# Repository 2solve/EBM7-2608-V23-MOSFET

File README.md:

# IC2S EBM7-2608 V2.3 — variante configurável 0-10 V / 4-20 mA (MOSFET)

Placa de extensão da família IC2S (Extension Board Model 7) com **quatro entradas analógicas configuráveis por software**
(cada uma em 0-10 V **ou** 4-20 mA), **uma entrada de célula de carga** e **um NTC de junta fria**, medidos por um ADC
sigma-delta de 24 bits (**AD7124-8**). Encaixa por baixo na base board: **P1** é o barramento (24 V, 5 V, SPI) e **P2** leva os
sinais de campo.

É a irmã da variante fixa 4-20 mA (repositório `2solve/EBM7-2608-V3`): mesma placa, mesmo layout de base, mais um MOSFET por
canal para escolher o modo e uma protecção completa da alimentação dos sensores.

Projecto KiCad 10 (testado em 10.0.5). Abrir
`Desenvolvimento_IC2S-EBM7-2608-V2.3-MOSFET/Projeto_IC2S-EBM7-2608-V2.3-MOSFET/IC2S-EBM7-2608-V2.3-MOSFET.kicad_pro`.

Identificador desta versão: **`IC2S-EBM7-2608-V2.3-MOSFET`**.

---

## Estado (28-09-2026)

| Verificação | Resultado |
|---|---|
| ERC | 0 erros |
| DRC (`--severity-all --schematic-parity`) | **0 erros**, 67 avisos (serigrafia) |
| Ligações por fazer | **48** |
| Paridade esquemático ↔ PCB | **1** (C35, ver [Pendentes](#pendentes)) |

**O esquemático está fechado; a placa não.** A PCB foi construída sobre a da variante fixa: as 148 peças comuns estão na mesma
posição e com as mesmas pistas; as **20 peças que só existem nesta variante** estão juntas num rectângulo à direita da placa,
à espera de serem colocadas e roteadas. Por isso as pastas de fabricação estão vazias.

---

## Estrutura do repositório

Padrão de pastas dos produtos da 2Solve (o mesmo de `Produtos/Axcel_Sensor`):

```
Desenvolvimento_IC2S-EBM7-2608-V2.3-MOSFET/
├── Projeto_IC2S-EBM7-2608-V2.3-MOSFET/
│   ├── IC2S-EBM7-2608-V2.3-MOSFET.kicad_pro / .kicad_sch / .kicad_pcb / .kicad_dru
│   ├── 01_conectores … 08_ntc.kicad_sch          (as oito folhas)
│   ├── footprints/EBM7_V23.pretty, symbols/       (bibliotecas locais, por ${KIPRJMOD})
│   ├── Documentos_de_Referência-…/                (33 datasheets + catálogo TDK de MLCC)
│   └── Outputs/drc_report.json
├── Documentos_IC2S-EBM7-2608-V2.3-MOSFET/
│   ├── 00-Especificações_Técnicas_…/   registos das alterações (25-09 e 28-09)
│   ├── 01-Esquemáticos_…/              Schematic-….pdf, ….step, …-Top_View.pdf, …-Bottom_View.pdf
│   ├── 02-Pinout_…/                    (vazio)
│   └── 03-Diagrama_Blocos_…/           (vazio)
└── Arquivos_Fabricação_IC2S-EBM7-2608-V2.3-MOSFET/
    ├── 00-Gerbers_…/  01-BOM_List_…/  02-Pick-and-Place_…/  03-Stencil_…/   (vazios até a placa estar roteada)
```

**Onde está cada decisão:** cada folha tem um bloco «DECISOES DESTA FOLHA» com notas numeradas; aqui cita-se *folha N, nota M*.

---

## O que é igual à variante fixa

Os blocos seguintes são os mesmos da fixa (lá estão explicados em detalhe); aqui só as referências, que mudam entre projectos:

| Bloco | Nesta placa |
|---|---|
| Entrada 24 V | **ramo único** (28-09-2026, folha 2, nota 13): TVS **D200** SMA6J33A-Q (clamp real 53,3 V) → fusível **F1** CC12H750MA → díodo **D5** MBR1H100SF → +24V_ADC; **C13** 10 µF/100 V na entrada do U3 (Recom p.4 pede 3,3 µF/100 V se Vin > 50 V) |
| Massas | GND_24V fundido em GND_ADC (folha 2, nota 7); DGND é a massa do processador |
| Alimentação | **U3** R-78HB5.0 (+24V_ADC → 5 V), **U4** SPX3819 (+3.3V_ANA), **U8** SPX3819 (+3.3V do lado PLC; era MCP1824 até 28-09), **U14** TL431 que grampeia o +3.3V_ANA a ~3,6 V (folha 3, nota 14) |
| Barreira | **U5** ISO7141: separação de ruído, não isolamento (folha 4, nota 1); regra de 1,0 mm e keepouts no PCB |
| ADC | **U6** AD7124-8, referência **U7** ADR4525 2,5 V no REFIN2 (folha 5, nota 1) |
| Protector dos laços | **U9-U12** TPS26613, +Vs a 12 V de **U15** TPS7A4001 (folha 6, notas 9 e 16) |
| Célula | **H1**: 1-2 = 2,5 V, 3-4 = 5 V (omissão), 5-6 = 3,3 V; **D31** Schottky RB162MM-60; **R5** 68 Ω 1 W (folha 7, notas 15 e 16) |
| NTC | junta fria para termopar (folha 8) |

---

## O que muda: modo duplo por canal

Decisão da folha 6: caixa **«DECISAO 25-09-2026 - MODO DUPLO»** e nota 12. Firmware: folha 5, nota 10.

Cada canal tem **dois caminhos** no P2:

- **Alimentação do sensor** (pino par, `+24V_AINn`): +24V_ADC → fusível **F3-F6** (125 mA) → díodo **D32-D35**
  (MBR1H100SF) → borne, com o TVS **D13/D16/D19/D22** (SMBJ51A) junto ao conector.
- **Sinal** (pino ímpar, `AINn`): borne → TVS 824500301 → **TPS26613** → divisor **40k2 / 10k** (sempre ligado) e, em
  paralelo, **burden 100 Ω** comutado pelo MOSFET → ferrite → RC → clamps BAV199 → ADC.

| Modo | MOSFET (Q1-Q4, FDN337N) | O que o sinal vê | No ADC |
|---|---|---|---|
| **4-20 mA** | fechado (GPIO = 1) | 100 Ω ‖ 50,2 kΩ = 99,8 Ω → 2,00 V a 20 mA | tap 0,080-0,398 V, ganho 4, fim de escala 31,4 mA |
| **0-10 V** | aberto (GPIO = 0) | 50,2 kΩ de entrada | tap 1,99 V a 10 V, ganho 1, gama garantida 0,5-12,5 V |

- A porta de cada MOSFET é comandada por uma **saída digital do próprio AD7124** (P1-P4 = pinos 6-9), com 100 kΩ a GND. No
  arranque a porta está em 0: o canal começa em 0-10 V; com um transmissor 4-20 mA ligado há hiccup até o firmware
  configurar o modo (folha 6, nota 13).
- **D26-D29** (MMSZ4702, zener de 15 V) protegem o dreno do MOSFET contra os surtos do campo.
- Verificações (na caixa da folha 6): nota (2) da Tabela 8-2 do TPS26613 cumprida mesmo a 40 mA (3,99 V < 4,46 V); FDN337N
  com RDS(on) ≤ 0,082 Ω a 2,5 V (0,08 % da carga, vai na calibração); zener não conduz em serviço (corte do OUT a 12,3 V).
- **Limitação:** abaixo de 0,5 V, em 0-10 V, o ADC com buffer e ganho 1 sai da especificação (AVSS + 0,1 V). Alternativa
  avaliada e **não aplicada** (muda o firmware): divisor 90k9/10k com ganho 2 em 0-10 V e ganho 8 em 4-20 mA.

**Mapa de canais** (da netlist):

| Canal de campo (P2) | Entrada do ADC | Saída que comanda o modo |
|---|---|---|
| AIN1 (P2.7) | AIN0 (pino 4) | P4 (pino 9) → MODO_AIN1 → Q1 |
| AIN2 (P2.9) | AIN1 (pino 5) | P3 (pino 8) → MODO_AIN2 → Q2 |
| AIN3 (P2.11) | AIN7 (pino 11) | P2 (pino 7) → MODO_AIN3 → Q3 |
| AIN4 (P2.13) | AIN6 (pino 10) | P1 (pino 6) → MODO_AIN4 → Q4 |
| Célula +/− | AIN10 / AIN11 | — |

## O que muda: protecção da alimentação dos sensores

Folha 6, nota 1, e folha 2, nota 9. Na variante fixa o fusível fica entre dois sumidouros de corrente (os condensadores do
bus e o TVS do borne) e um surto forte abre-o. Aqui:

- o **díodo em série** (D32-D35) impede que um surto do campo volte para o bus;
- o **SMBJ51A** (V_BR ≥ 56,7 V) não conduz nos surtos do bus, porque o TVS de entrada D200 grampeia a ≤ 53,3 V;
- assim a corrente de clamp **nunca passa pelo fusível**. Custo: ~0,5 V de queda na alimentação do sensor.

## Alterações de 28-09-2026 (reunião)

| O quê | Porquê |
|---|---|
| **Ramo único de 24 V**: saem F2, D1 e C1; F1 + D5 alimentam o U3 e o +24V_ADC; +24V_REG deixa de existir | reunião: é tudo alimentado pelos mesmos 24 V, não eram canais independentes nem isolados; ganha-se espaço |
| 100 nF fora do 24 V → TDK C1608X7R1H104K080AA (50 V), 24 peças; o C6 (+24V_ADC) fica GRM188R72A104KA35D (100 V) | 100 V estava sobredimensionado; pior caso fora do 24 V é o +12V_TPS a 31,7 V, por isso 50 V e não 25 V |
| 1 µF → TDK C1608X7R1H105K080AB (50 V) nos quatro | havia dois MPN para a mesma função |
| U8 MCP1824ST (SOT-223) → SPX3819 (SOT-23-5); faltam rotear as ligações do U8 e do C61 (2,2 µF na saída, como a V2.2) | mesmo MPN do U4 (`alteracao_LDO_3V3_lado_PLC_2026-09-28.md`) |

Condensadores: folha 2, nota 14. O catálogo TDK usado está em `Documentos_de_Referência-…/TDK_mlcc_commercial_general_en.pdf`
(p.34 para o 100 nF, p.35 para o 1 µF).

## Outras diferenças

- **C56 = 10 µF / 100 V em 1210** (GRM32EC72A106ME05L): condensador de entrada do U15 junto ao pino (SBVS162B pede > 1 µF
  efectivo).
- Footprint do **U15** conforme o land pattern da TI (SBVS162B p.22), com excepção dos pads NC no `.kicad_dru`.

---

## Placa (PCB)

- 60 × 60 mm, 4 camadas: F.Cu sinal · In1/In2 planos de massa partidos (DGND | GND_ADC) · B.Cu sinal e massa.
- Colocação, pistas, vias, zonas e keepouts das 148 peças comuns copiados da variante fixa (25-09-2026). 50 pistas da fixa
  **não** foram copiadas porque aqui dariam curto (saídas de F3-F6 antes do díodo; pinos do ADC que passaram a ser GPIO).

---

## Notas do esquemático desactualizadas

- **Folha 6, notas 13 e 14:** dizem AO3400A e BZT52H-C15; as peças montadas são **FDN337N** e **MMSZ4702T1G** (verificadas
  contra os datasheets na caixa «DECISAO 25-09»).
- **Folha 3, nota 1:** diz U3 = K78U05; a peça é o **R-78HB5.0-0.5L**.
- **Folha 7, nota 11:** diz TPS7A2025 para o U13; a peça montada é o **LP5907MFX-2.5**.

---

## Documentos

Em `Documentos_…/00-Especificações_Técnicas_IC2S-EBM7-2608-V2.3-MOSFET/`:

| Ficheiro | Conteúdo |
|---|---|
| `alteracoes_esquematico_e_PCB_2026-09-25.md` | registo das alterações de 25-09: modo duplo reposto, correcções vindas da fixa, verificação do FDN337N/MMSZ4702, importação e colocação da PCB |
| `alteracoes_reuniao_2026-09-28.md` | revisão da reunião de 28-09: ramo único de 24 V, entrada do R-78HB, tensão dos 100 nF, MPN do 1 µF |

---

## Pendentes

- **Paridade C35:** o pad 2 do C35 está ligado por pista a +3.3V_ANA (via em 162,25; 84,65 → pad), mas no esquemático é
  GND_ADC (é o condensador de filtro de AIN5 para a massa). Corrigir a pista na PCB.
- **Colocar as 20 peças** do rectângulo «SO CONFIGURAVEL» (fila = canal) junto de cada TPS26613 e do seu fusível, e **rotear
  as 48 ligações** que faltam.
- Serigrafia (67 avisos).
- Gerar Gerbers, BOM, pick-and-place e stencil quando a placa estiver roteada.
- Datasheets em falta: SMBJ51A-13-F (Diodes), MBR1H100SFT3G (onsemi), BLM18PG471SN1D (Murata), LED KG EELP41.22,
  resistências genéricas.
- Revisão independente do roteamento (`2shw-pcb:check-roteamento`) antes de fabricar.
- O mecanismo da avaria em campo da V2.2 não foi medido (G8).

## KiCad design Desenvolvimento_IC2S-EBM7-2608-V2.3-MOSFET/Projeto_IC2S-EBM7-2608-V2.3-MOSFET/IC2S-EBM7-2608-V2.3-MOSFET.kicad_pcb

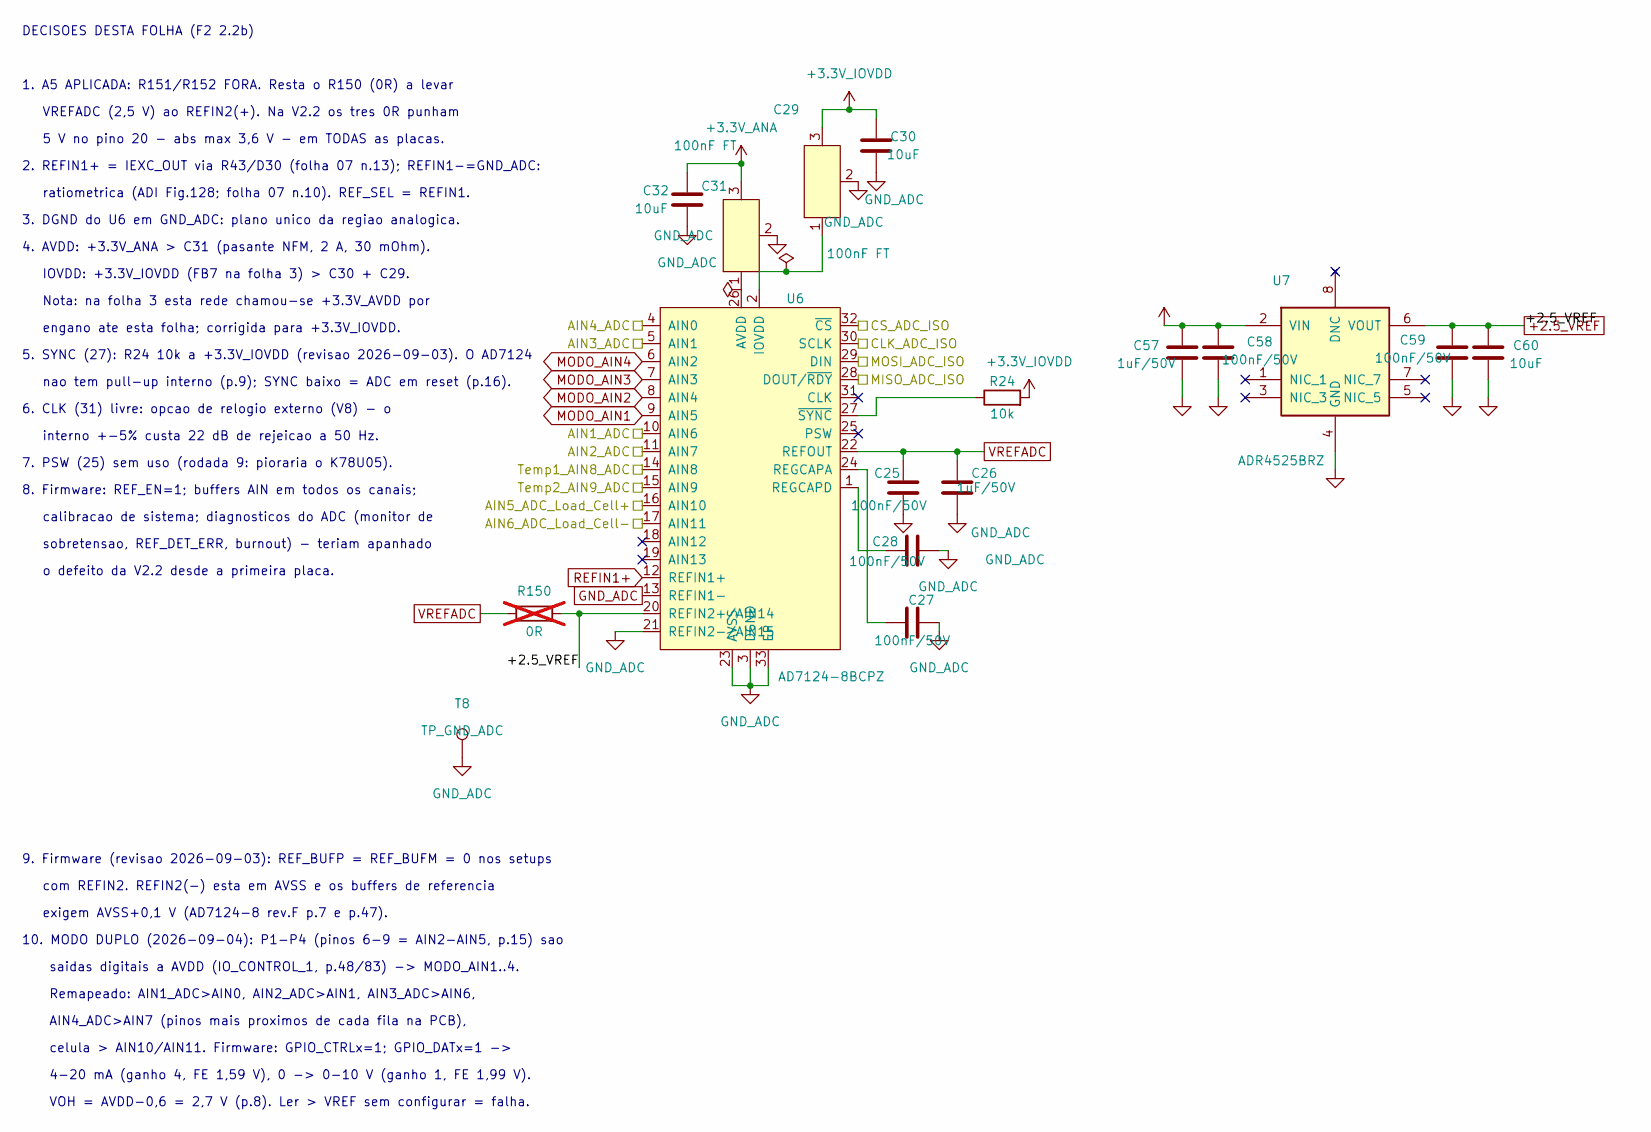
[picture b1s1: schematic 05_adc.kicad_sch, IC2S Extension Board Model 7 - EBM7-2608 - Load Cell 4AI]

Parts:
C25, C27, C28, C58, C59: 100nF/50V; 0603C; MPN C1608X7R1H104K080AA
C26, C57: 1uF/50V; 0603C; MPN C1608X7R1H105K080AB
C29, C31: 100nF FT; NFM0603; MPN NFM18PC104R1C3D
C30, C32, C60: 10uF; 0603C; MPN 0603YD106KAT2A
R24: 10k; 0603R; MPN RC0603FR-0710KL
R150: 0R; 0603R; MPN RC0603JR-070RL; not fitted
T8: TP_GND_ADC; TestPad_Via
U6: AD7124-8BCPZ; LFCSP-32-2; MPN AD7124-8BCPZ
U7: ADR4525BRZ; SOIC8; MPN ADR4525BRZ

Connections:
+2.5_VREF: C59.1, C60.1, R150.2, U6.20 (REFIN2+/AIN14), U7.6 (VOUT)
+3.3V_IOVDD: C29.3 (OUT), C30.2, R24.2; also elsewhere on the board
/4 Barreira digital/CLK_ADC_ISO: U6.30 (SCLK); also elsewhere on the board
/4 Barreira digital/CS_ADC_ISO: U6.32 (~CS); also elsewhere on the board
/4 Barreira digital/MISO_ADC_ISO: U6.28 (DOUT/~RDY); also elsewhere on the board
/4 Barreira digital/MOSI_ADC_ISO: U6.29 (DIN); also elsewhere on the board
/5 ADC/AIN1_ADC: U6.10 (AIN6); also elsewhere on the board
/5 ADC/AIN2_ADC: U6.11 (AIN7); also elsewhere on the board
/5 ADC/AIN3_ADC: U6.5 (AIN1); also elsewhere on the board
/5 ADC/AIN4_ADC: U6.4 (AIN0); also elsewhere on the board
/5 ADC/AIN5_ADC_Load_Cell+: U6.16 (AIN10); also elsewhere on the board
/5 ADC/AIN6_ADC_Load_Cell-: U6.17 (AIN11); also elsewhere on the board
/5 ADC/Temp1_AIN8_ADC: U6.14 (AIN8); also elsewhere on the board
/5 ADC/Temp2_AIN9_ADC: U6.15 (AIN9); also elsewhere on the board
MODO_AIN1: U6.9 (AIN5); also elsewhere on the board
MODO_AIN2: U6.8 (AIN4); also elsewhere on the board
MODO_AIN3: U6.7 (AIN3); also elsewhere on the board
MODO_AIN4: U6.6 (AIN2); also elsewhere on the board
unnamed: C29.1 (IN), U6.2 (IOVDD)
unnamed: C31.1 (IN), U6.26 (AVDD)
unnamed: C27.2, U6.24 (REGCAPA)
unnamed: C28.2, U6.1 (REGCAPD)
unnamed: R24.1, U6.27 (~SYNC)
REFIN1+: U6.12 (REFIN1+); also elsewhere on the board
VREFADC: C25.2, C26.1, R150.1, U6.22 (REFOUT); also elsewhere on the board

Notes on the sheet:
celula > AIN10/AIN11. Firmware: GPIO_CTRLx=1; GPIO_DATx=1 ->
ratiometrica (ADI Fig.128; folha 07 n.10). REF_SEL = REFIN1.
4. AVDD: +3.3V_ANA > C31 (pasante NFM, 2 A, 30 mOhm).
engano ate esta folha; corrigida para +3.3V_IOVDD.
Nota: na folha 3 esta rede chamou-se +3.3V_AVDD por
com REFIN2. REFIN2(-) esta em AVSS e os buffers de referencia
1. A5 APLICADA: R151/R152 FORA. Resta o R150 (0R) a levar
Remapeado: AIN1_ADC>AIN0, AIN2_ADC>AIN1, AIN3_ADC>AIN6,
calibracao de sistema; diagnosticos do ADC (monitor de
sobretensao, REF_DET_ERR, burnout) - teriam apanhado
saidas digitais a AVDD (IO_CONTROL_1, p.48/83) -> MODO_AIN1..4.
AIN4_ADC>AIN7 (pinos mais proximos de cada fila na PCB),
2. REFIN1+ = IEXC_OUT via R43/D30 (folha 07 n.13); REFIN1-=GND_ADC:
interno +-5% custa 22 dB de rejeicao a 50 Hz.
VREFADC (2,5 V) ao REFIN2(+). Na V2.2 os tres 0R punham
DECISOES DESTA FOLHA (F2 2.2b)
3. DGND do U6 em GND_ADC: plano unico da regiao analogica.
6. CLK (31) livre: opcao de relogio externo (V8) - o
10. MODO DUPLO (2026-09-04): P1-P4 (pinos 6-9 = AIN2-AIN5, p.15) sao
IOVDD: +3.3V_IOVDD (FB7 na folha 3) > C30 + C29.
o defeito da V2.2 desde a primeira placa.
nao tem pull-up interno (p.9); SYNC baixo = ADC em reset (p.16).
5. SYNC (27): R24 10k a +3.3V_IOVDD (revisao 2026-09-03). O AD7124
8. Firmware: REF_EN=1; buffers AIN em todos os canais;
VOH = AVDD-0,6 = 2,7 V (p.8). Ler > VREF sem configurar = falha.
7. PSW (25) sem uso (rodada 9: pioraria o K78U05).
5 V no pino 20 - abs max 3,6 V - em TODAS as placas.
exigem AVSS+0,1 V (AD7124-8 rev.F p.7 e p.47).
4-20 mA (ganho 4, FE 1,59 V), 0 -> 0-10 V (ganho 1, FE 1,99 V).
9. Firmware (revisao 2026-09-03): REF_BUFP = REF_BUFM = 0 nos setups

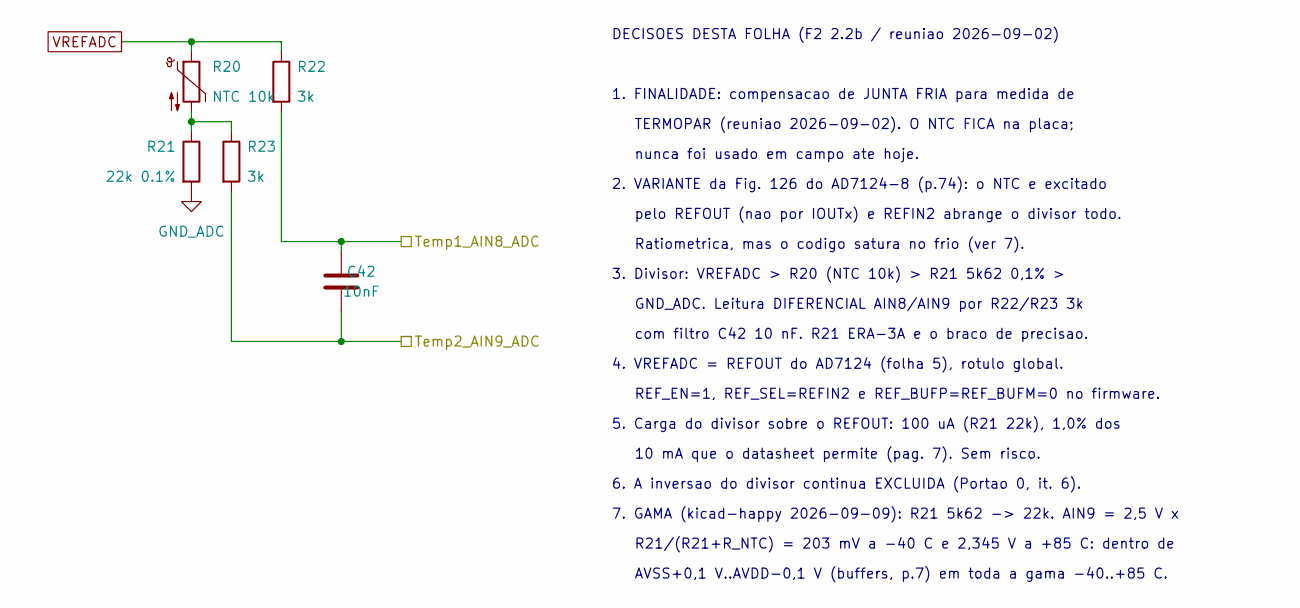
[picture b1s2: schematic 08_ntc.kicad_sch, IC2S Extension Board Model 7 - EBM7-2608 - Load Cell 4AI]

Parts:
C42: 10nF; 0603C; MPN GCM188R71H103KA37J
R20: NTC 10k; 0603R; MPN NTCS0603E3103JLT
R21: 22k 0.1%; 0603R; MPN RG1608P-223-B-T5
R22, R23: 3k; 0603R; MPN RC0603FR-073KL

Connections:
/5 ADC/Temp1_AIN8_ADC: C42.2, R22.2; also elsewhere on the board
/5 ADC/Temp2_AIN9_ADC: C42.1, R23.2; also elsewhere on the board
unnamed: R20.2, R21.1, R23.1
VREFADC: R20.1, R22.1; also elsewhere on the board

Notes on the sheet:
GND_ADC. Leitura DIFERENCIAL AIN8/AIN9 por R22/R23 3k
pelo REFOUT (nao por IOUTx) e REFIN2 abrange o divisor todo.
5. Carga do divisor sobre o REFOUT: 100 uA (R21 22k), 1,0% dos
Ratiometrica, mas o codigo satura no frio (ver 7).
4. VREFADC = REFOUT do AD7124 (folha 5), rotulo global.
nunca foi usado em campo ate hoje.
R21/(R21+R_NTC) = 203 mV a -40 C e 2,345 V a +85 C: dentro de
1. FINALIDADE: compensacao de JUNTA FRIA para medida de
2. VARIANTE da Fig. 126 do AD7124-8 (p.74): o NTC e excitado
REF_EN=1, REF_SEL=REFIN2 e REF_BUFP=REF_BUFM=0 no firmware.
10 mA que o datasheet permite (pag. 7). Sem risco.
3. Divisor: VREFADC > R20 (NTC 10k) > R21 5k62 0,1% >
DECISOES DESTA FOLHA (F2 2.2b / reuniao 2026-09-02)
6. A inversao do divisor continua EXCLUIDA (Portao 0, it. 6).
com filtro C42 10 nF. R21 ERA-3A e o braco de precisao.
TERMOPAR (reuniao 2026-09-02). O NTC FICA na placa;
7. GAMA (kicad-happy 2026-09-09): R21 5k62 -> 22k. AIN9 = 2,5 V x
AVSS+0,1 V..AVDD-0,1 V (buffers, p.7) em toda a gama -40..+85 C.

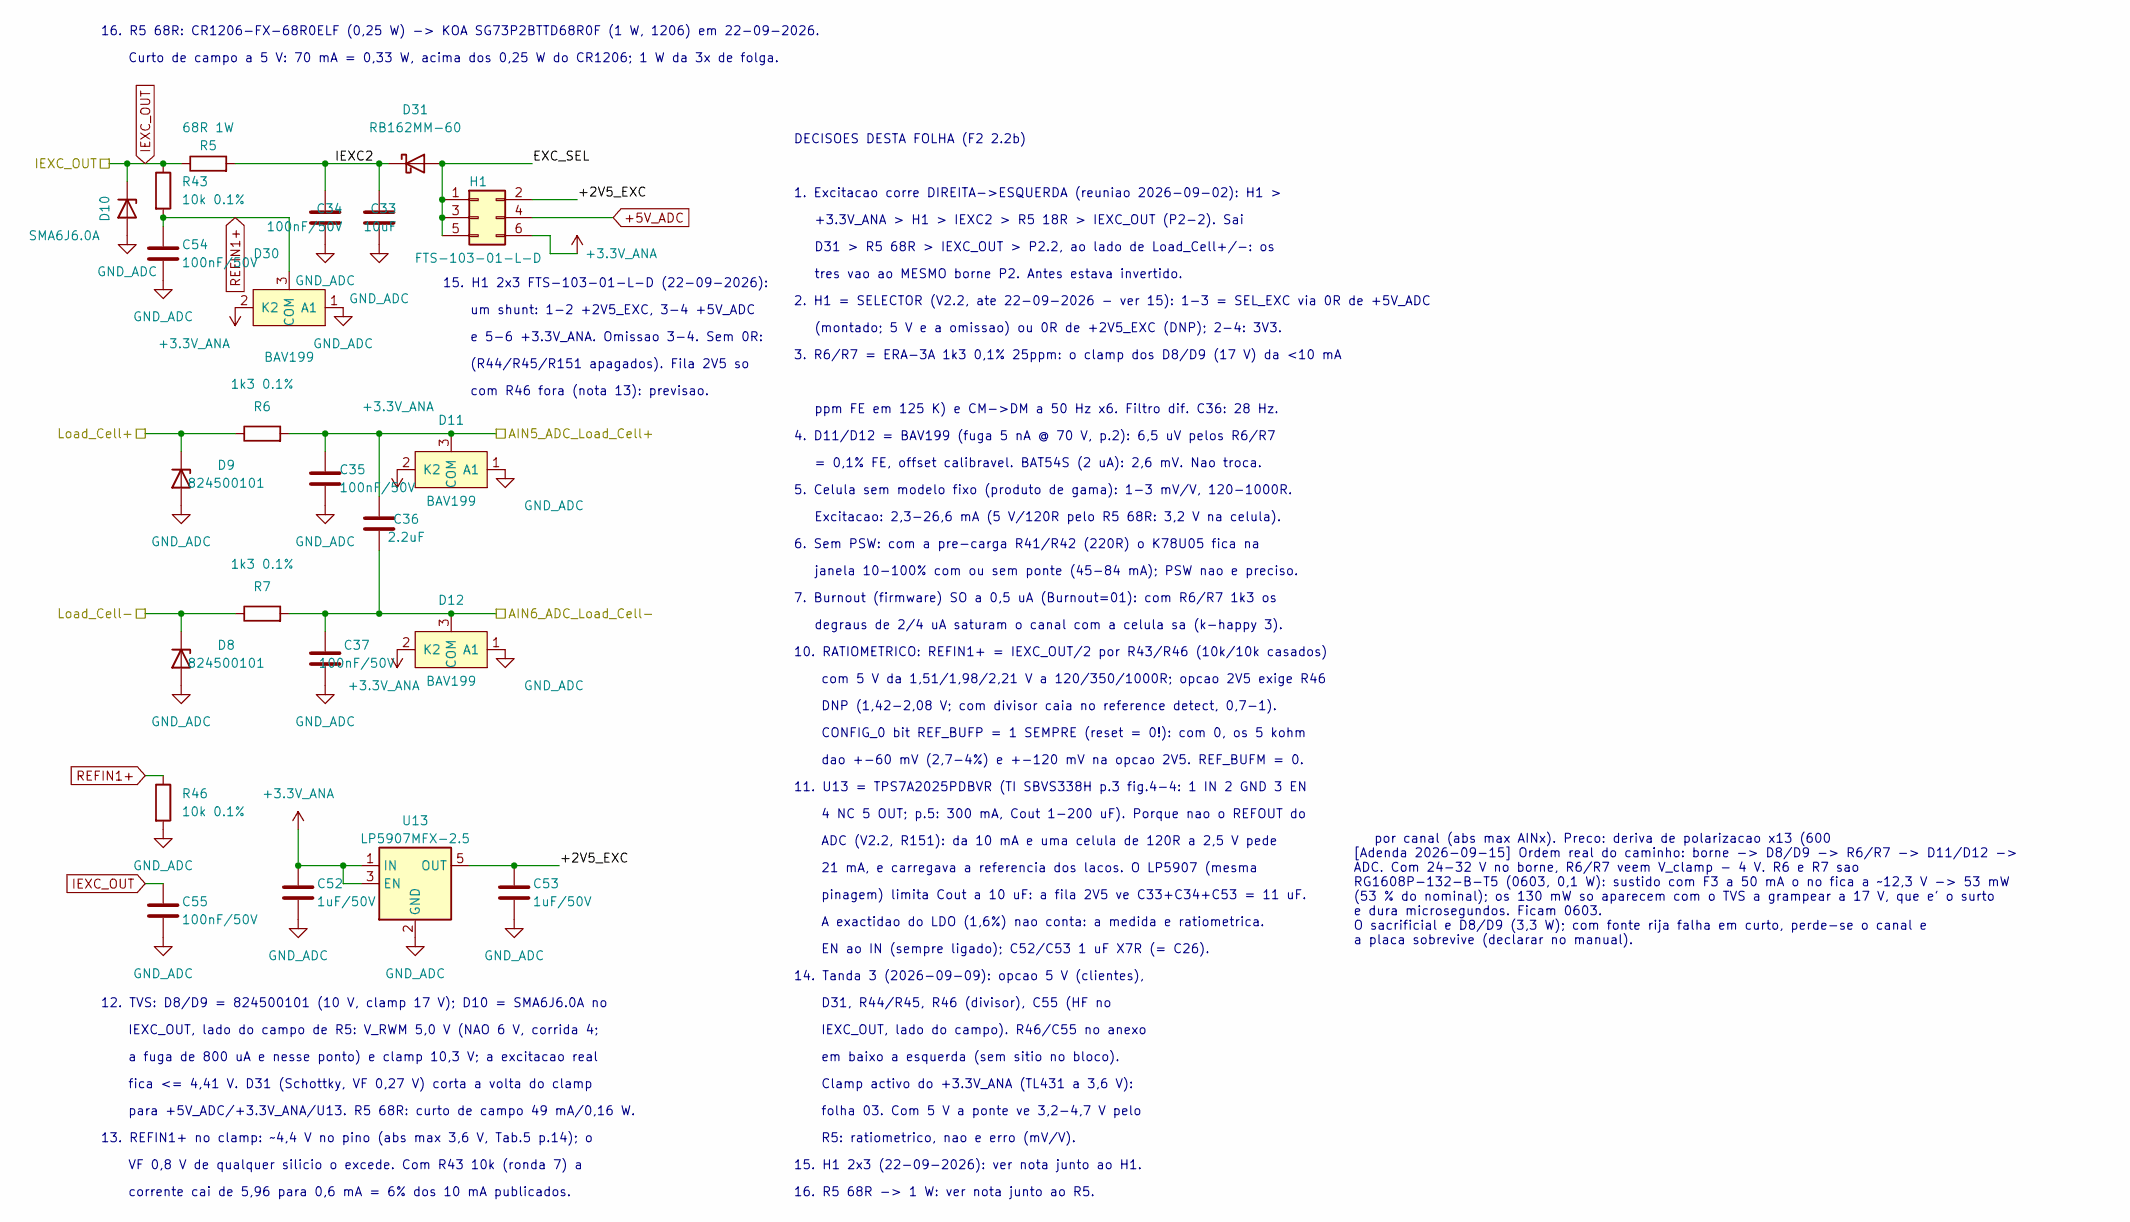
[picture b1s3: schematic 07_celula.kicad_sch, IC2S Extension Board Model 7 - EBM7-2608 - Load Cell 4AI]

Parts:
C33: 10uF; 0603C; MPN 0603YD106KAT2A
C34, C35, C37, C54, C55: 100nF/50V; 0603C; MPN C1608X7R1H104K080AA
C36: 2.2uF; 0603C; MPN C1608X5R1E225K080AB
C52, C53: 1uF/50V; 0603C; MPN C1608X7R1H105K080AB
D8, D9: 824500101; DO-214; MPN 824500101
D10: SMA6J6.0A; DO-214; MPN SMA6J6.0A
D11, D12, D30: BAV199; SOT23-3; MPN BAV199LT1G
D31: RB162MM-60; SOD-123F; MPN RB162MM-60TR
H1: FTS-103-01-L-D; HDR2X3_1.27mm-Without_number; MPN FTS-103-01-L-D
R5: 68R 1W; 1206R; MPN SG73P2BTTD68R0F
R6, R7: 1k3 0.1%; 0603R; MPN RG1608P-132-B-T5
R43, R46: 10k 0.1%; 0603R; MPN RG1608P-103-B-T5
U13: LP5907MFX-2.5; SOT-23-5; MPN LP5907MFX-2.5/NOPB

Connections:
+5V_ADC: H1.4; also elsewhere on the board
/1 Conectores/Load_Cell+: D9.1 (K), R6.1; also elsewhere on the board
/1 Conectores/Load_Cell-: D8.1 (K), R7.1; also elsewhere on the board
/5 ADC/AIN5_ADC_Load_Cell+: C35.1, C36.2, D11.3 (COM), R6.2; also elsewhere on the board
/5 ADC/AIN6_ADC_Load_Cell-: C36.1, C37.2, D12.3 (COM), R7.2; also elsewhere on the board
/7 Celula de carga/+2V5_EXC: C53.1, H1.2, U13.5 (OUT)
/7 Celula de carga/EXC_SEL: D31.2 (A), H1.1, H1.3, H1.5
/7 Celula de carga/IEXC2: C33.2, C34.2, D31.1 (K), R5.2
IEXC_OUT: C55.1, D10.1 (K), R5.1, R43.1; also elsewhere on the board
REFIN1+: C54.1, D30.3 (COM), R43.2, R46.1; also elsewhere on the board

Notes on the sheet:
ADC (V2.2, R151): da 10 mA e uma celula de 120R a 2,5 V pede
14. Tanda 3 (2026-09-09): opcao 5 V (clientes),
folha 03. Com 5 V a ponte ve 3,2-4,7 V pelo
12. TVS: D8/D9 = 824500101 (10 V, clamp 17 V); D10 = SMA6J6.0A no
IEXC_OUT, lado do campo). R46/C55 no anexo
fica <= 4,41 V. D31 (Schottky, VF 0,27 V) corta a volta do clamp
dao +-60 mV (2,7-4%) e +-120 mV na opcao 2V5. REF_BUFM = 0.
a fuga de 800 uA e nesse ponto) e clamp 10,3 V; a excitacao real
Clamp activo do +3.3V_ANA (TL431 a 3,6 V):
EN ao IN (sempre ligado); C52/C53 1 uF X7R (= C26).
13. REFIN1+ no clamp: ~4,4 V no pino (abs max 3,6 V, Tab.5 p.14); o
com 5 V da 1,51/1,98/2,21 V a 120/350/1000R; opcao 2V5 exige R46
corrente cai de 5,96 para 0,6 mA = 6% dos 10 mA publicados.
5. Celula sem modelo fixo (produto de gama): 1-3 mV/V, 120-1000R.
4. D11/D12 = BAV199 (fuga 5 nA @ 70 V, p.2): 6,5 uV pelos R6/R7
7. Burnout (firmware) SO a 0,5 uA (Burnout=01): com R6/R7 1k3 os
VF 0,8 V de qualquer silicio o excede. Com R43 10k (ronda 7) a
A exactidao do LDO (1,6%) nao conta: a medida e ratiometrica.
4 NC 5 OUT; p.5: 300 mA, Cout 1-200 uF). Porque nao o REFOUT do
3. R6/R7 = ERA-3A 1k3 0,1% 25ppm: o clamp dos D8/D9 (17 V) da <10 mA
em baixo a esquerda (sem sitio no bloco).
2. H1 = SELECTOR (V2.2, ate 22-09-2026 - ver 15): 1-3 = SEL_EXC via 0R de +5V_ADC
degraus de 2/4 uA saturam o canal com a celula sa (k-happy 3).
CONFIG_0 bit REF_BUFP = 1 SEMPRE (reset = 0!): com 0, os 5 kohm
Excitacao: 2,3-26,6 mA (5 V/120R pelo R5 68R: 3,2 V na celula).
para +5V_ADC/+3.3V_ANA/U13. R5 68R: curto de campo 49 mA/0,16 W.
IEXC_OUT, lado do campo de R5: V_RWM 5,0 V (NAO 6 V, corrida 4;
R5: ratiometrico, nao e erro (mV/V).
1. Excitacao corre DIREITA->ESQUERDA (reuniao 2026-09-02): H1 >
D31 > R5 68R > IEXC_OUT > P2.2, ao lado de Load_Cell+/-: os
DNP (1,42-2,08 V; com divisor caia no reference detect, 0,7-1).
+3.3V_ANA > H1 > IEXC2 > R5 18R > IEXC_OUT (P2-2). Sai
ppm FE em 125 K) e CM->DM a 50 Hz x6. Filtro dif. C36: 28 Hz.
por canal (abs max AINx). Preco: deriva de polarizacao x13 (600 [Adenda 2026-09-15] Ordem real do caminho: borne -> D8/D9 -> R6/R7 -> D11/D12 -> ADC. Com 24-32 V no borne, R6/R7 veem V_clamp - 4 V. R6 e R7 sao RG1608P-132-B-T5 (0603, 0,1 W): sustido com F3 a 50 mA o no fica a ~12,3 V -> 53 mW (53 %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
6. Sem PSW: com a pre-carga R41/R42 (220R) o K78U05 fica na
janela 10-100% com ou sem ponte (45-84 mA); PSW nao e preciso.
= 0,1% FE, offset calibravel. BAT54S (2 uA): 2,6 mV. Nao troca.
10. RATIOMETRICO: REFIN1+ = IEXC_OUT/2 por R43/R46 (10k/10k casados)
21 mA, e carregava a referencia dos lacos. O LP5907 (mesma
11. U13 = TPS7A2025PDBVR (TI SBVS338H p.3 fig.4-4: 1 IN 2 GND 3 EN

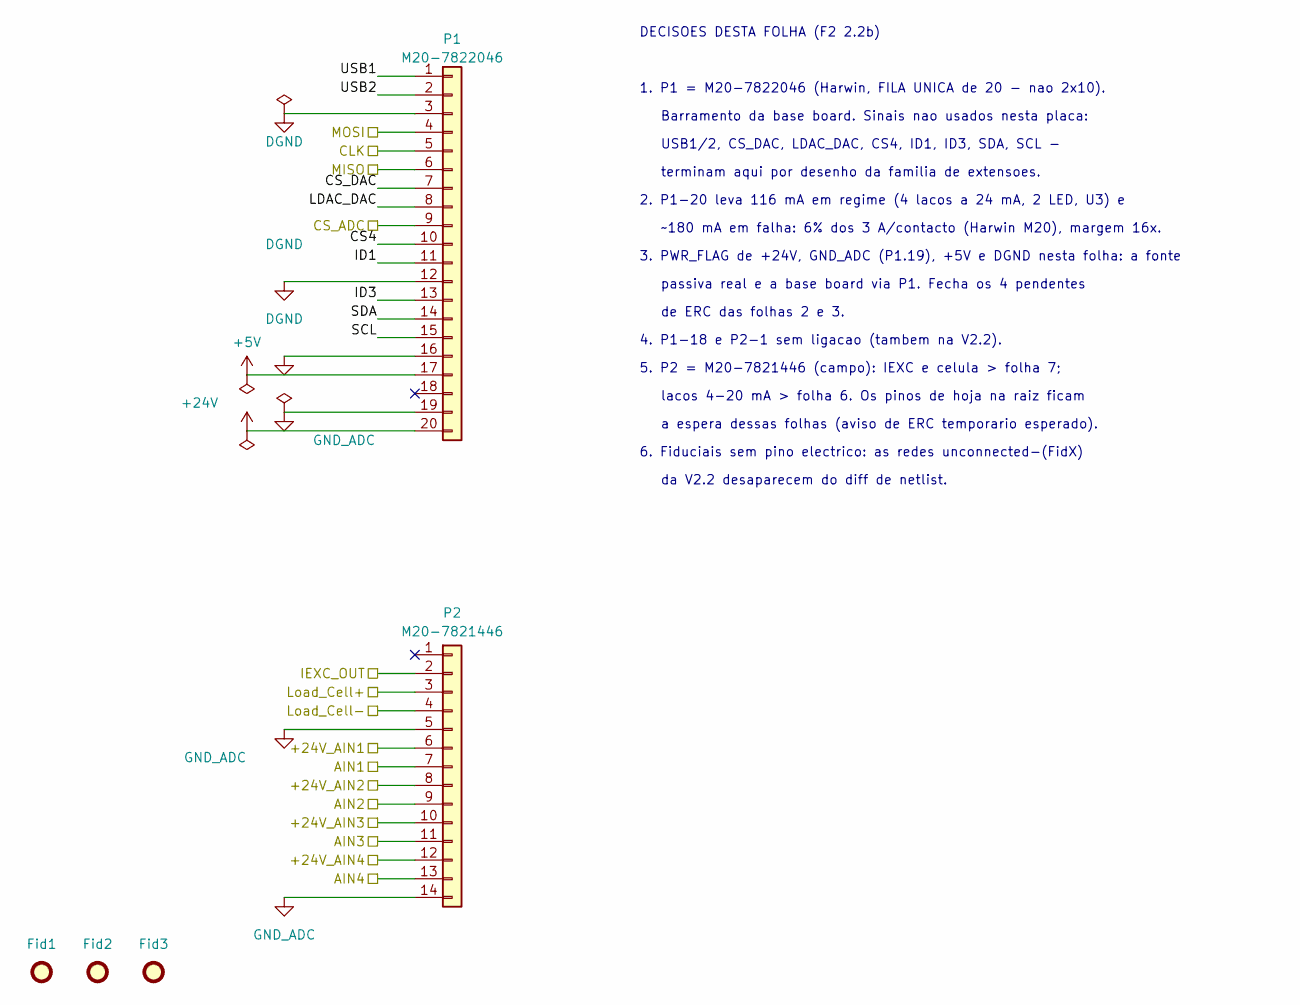
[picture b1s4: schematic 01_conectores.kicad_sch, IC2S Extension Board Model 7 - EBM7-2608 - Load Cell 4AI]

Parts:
Fid1, Fid2, Fid3: Fiducial; Fiducial_Point_Top-Bot
P1: M20-7822046; HDR1X20_FEMALE; MPN M20-7822046
P2: M20-7821446; HDR1X14_FEMALE; MPN M20-7821446

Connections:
+5V: P1.17; also elsewhere on the board
+24V: P1.20; also elsewhere on the board
/1 Conectores/+24V_AIN1: P2.6; also elsewhere on the board
/1 Conectores/+24V_AIN2: P2.8; also elsewhere on the board
/1 Conectores/+24V_AIN3: P2.10; also elsewhere on the board
/1 Conectores/+24V_AIN4: P2.12; also elsewhere on the board
/1 Conectores/AIN1: P2.7; also elsewhere on the board
/1 Conectores/AIN2: P2.9; also elsewhere on the board
/1 Conectores/AIN3: P2.11; also elsewhere on the board
/1 Conectores/AIN4: P2.13; also elsewhere on the board
/1 Conectores/CS4: P1.10
/1 Conectores/CS_DAC: P1.7
/1 Conectores/ID1: P1.11
/1 Conectores/ID3: P1.13
/1 Conectores/LDAC_DAC: P1.8
/1 Conectores/Load_Cell+: P2.3; also elsewhere on the board
/1 Conectores/Load_Cell-: P2.4; also elsewhere on the board
/1 Conectores/SCL: P1.15
/1 Conectores/SDA: P1.14
/1 Conectores/USB1: P1.1
/1 Conectores/USB2: P1.2
/CLK: P1.5; also elsewhere on the board
/CS_ADC: P1.9; also elsewhere on the board
/MISO: P1.6; also elsewhere on the board
/MOSI: P1.4; also elsewhere on the board
DGND: P1.3, P1.12, P1.16; also elsewhere on the board
IEXC_OUT: P2.2; also elsewhere on the board

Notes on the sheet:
de ERC das folhas 2 e 3.
Barramento da base board. Sinais nao usados nesta placa:
4. P1-18 e P2-1 sem ligacao (tambem na V2.2).
lacos 4-20 mA > folha 6. Os pinos de hoja na raiz ficam
~180 mA em falha: 6% dos 3 A/contacto (Harwin M20), margem 16x.
USB1/2, CS_DAC, LDAC_DAC, CS4, ID1, ID3, SDA, SCL -
6. Fiduciais sem pino electrico: as redes unconnected-(FidX)
5. P2 = M20-7821446 (campo): IEXC e celula > folha 7;
1. P1 = M20-7822046 (Harwin, FILA UNICA de 20 - nao 2x10).
2. P1-20 leva 116 mA em regime (4 lacos a 24 mA, 2 LED, U3) e
da V2.2 desaparecem do diff de netlist.
DECISOES DESTA FOLHA (F2 2.2b)
passiva real e a base board via P1. Fecha os 4 pendentes
3. PWR_FLAG de +24V, GND_ADC (P1.19), +5V e DGND nesta folha: a fonte
terminam aqui por desenho da familia de extensoes.
a espera dessas folhas (aviso de ERC temporario esperado).

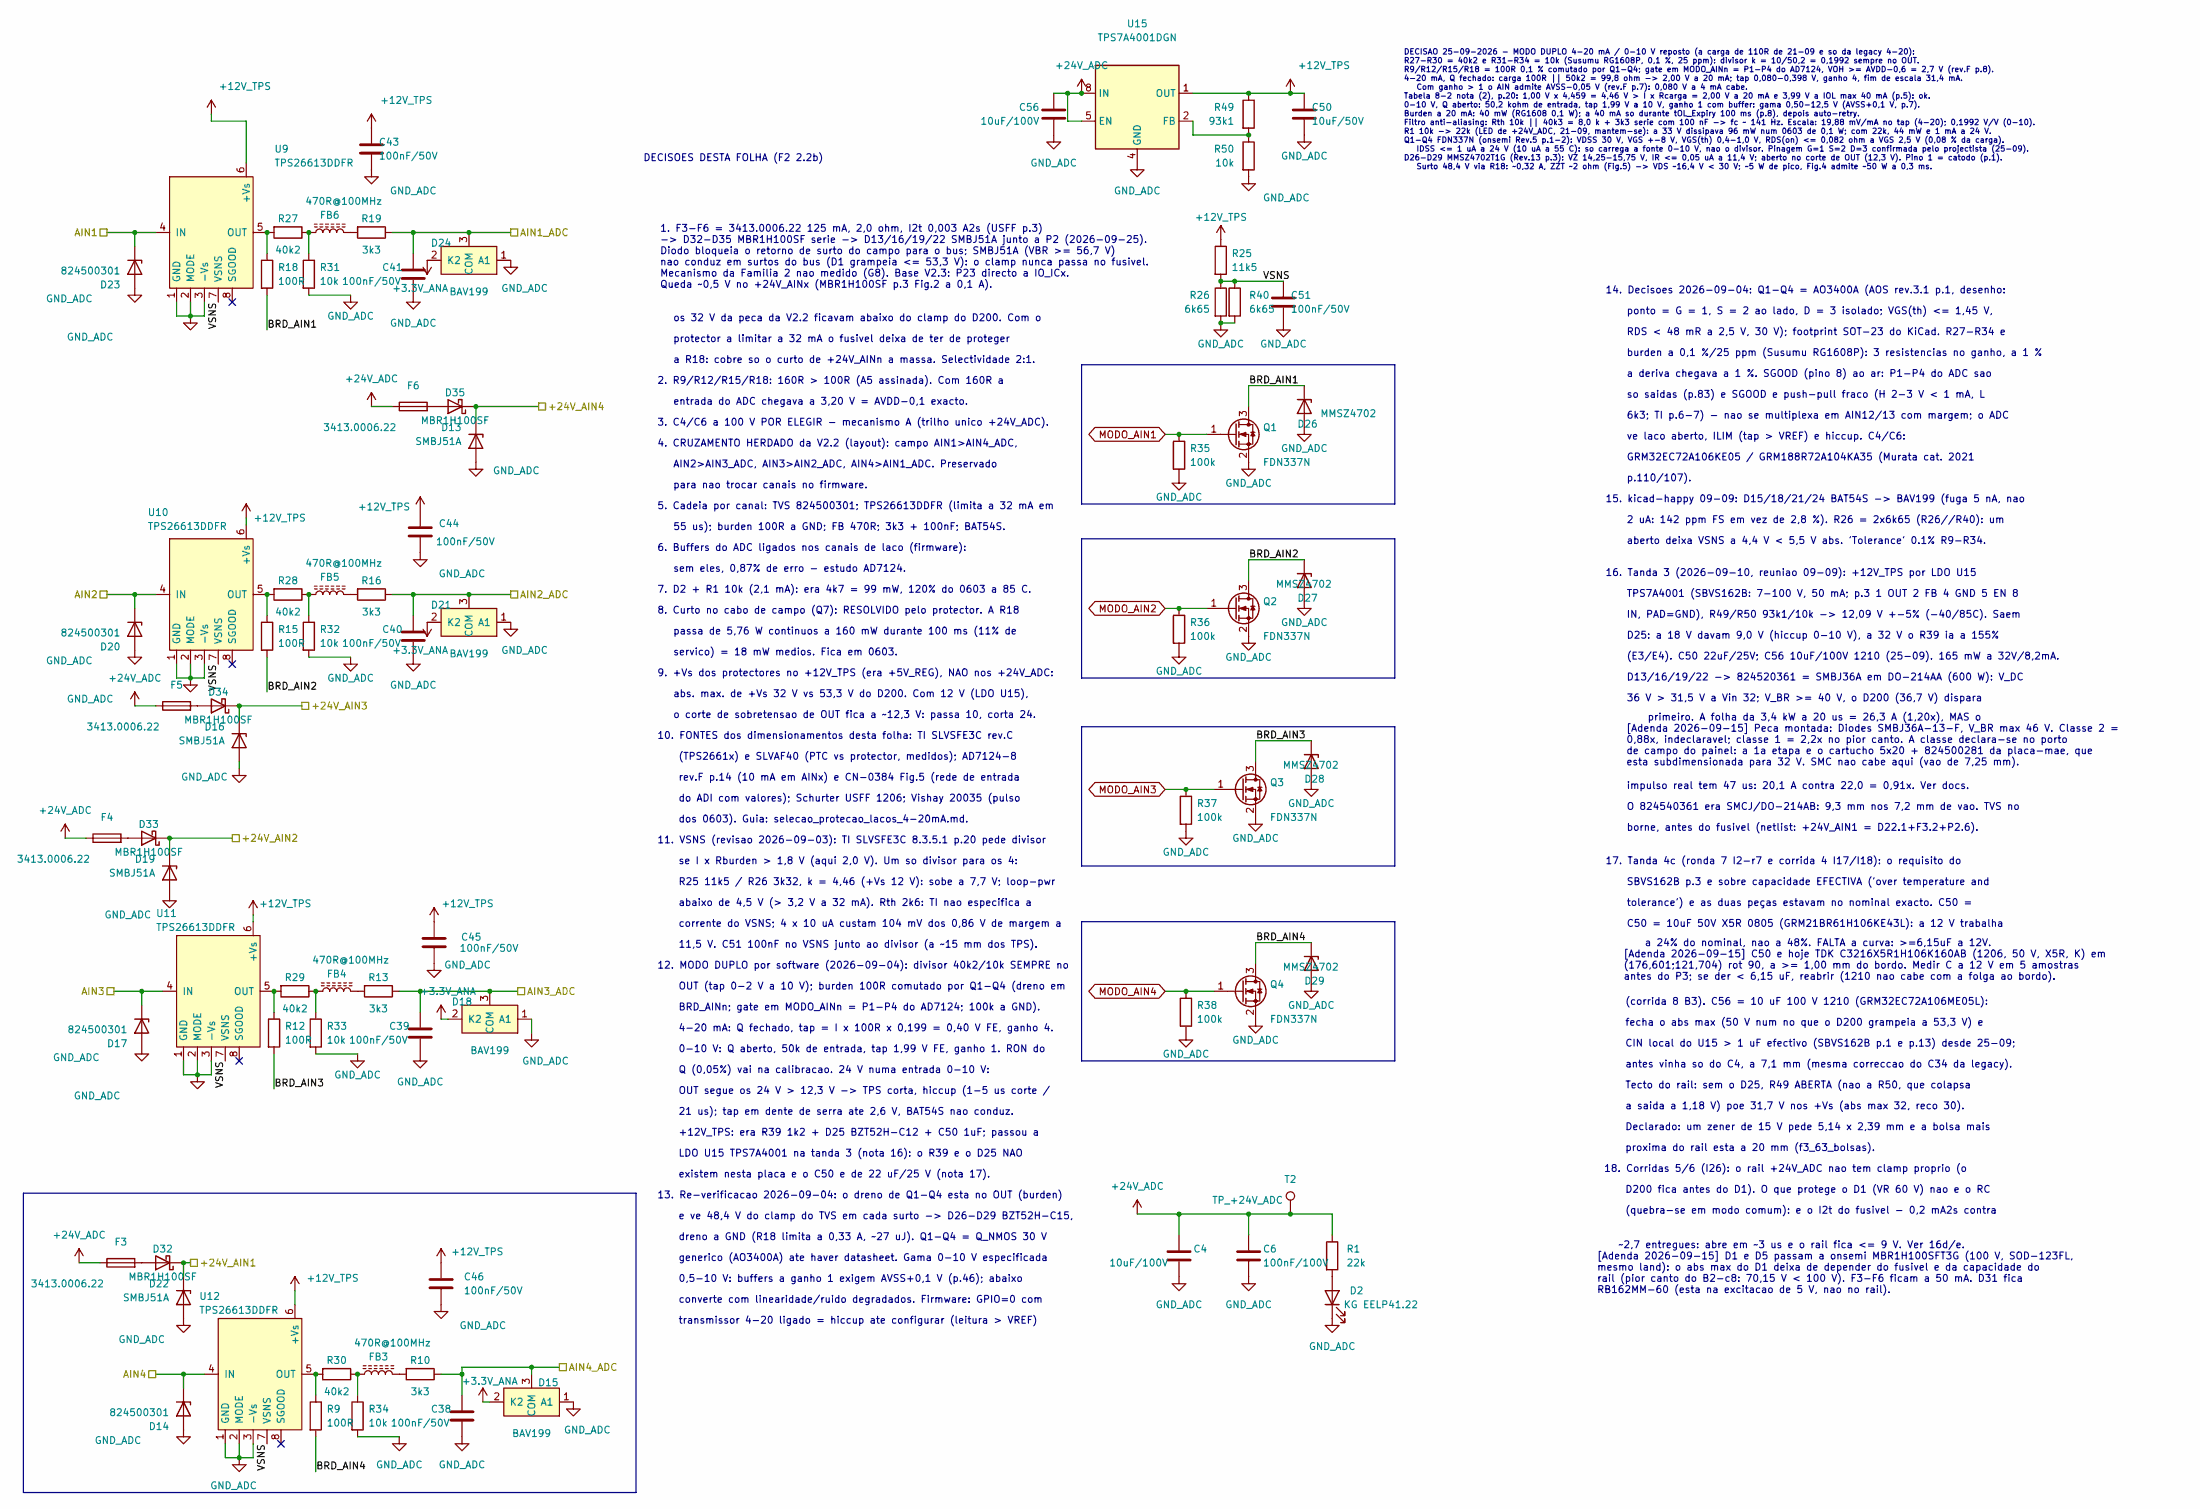
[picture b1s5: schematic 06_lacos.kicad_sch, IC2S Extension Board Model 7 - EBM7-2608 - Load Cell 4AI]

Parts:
C4, C56: 10uF/100V; C_1210_3225Metric; MPN GRM32EC72A106ME05L
C6: 100nF/100V; 0603C; MPN GRM188R72A104KA35D
C38, C39, C40, C41, C43, C44, C45, C46, C51: 100nF/50V; 0603C; MPN C1608X7R1H104K080AA
C50: 10uF/50V; C_1206_3216Metric; MPN C3216X5R1H106K160AB
D2: KG EELP41.22; 0603LED; MPN KG EELP41.22-PHRH-35-A8J8-20-R18
D13, D16, D19, D22: SMBJ51A; DO-214AA; MPN SMBJ51A-13-F
D14, D17, D20, D23: 824500301; DO-214; MPN 824500301
D15, D18, D21, D24: BAV199; SOT23-3; MPN BAV199LT1G
D26, D27, D28, D29: MMSZ4702; SOD123; MPN MMSZ4702T1G
D32, D33, D34, D35: MBR1H100SF; SOD123; MPN MBR1H100SFT3G
F3, F4, F5, F6: 3413.0006.22; 1206F; MPN 3413.0006.22
FB3, FB4, FB5, FB6: 470R@100MHz; 0603FB; MPN BLM18PG471SN1D
Q1, Q2, Q3, Q4: FDN337N; SOT-23; MPN FDN337N
R1: 22k; 0603R; MPN ERJ-3EKF2202V
R9, R12, R15, R18: 100R; 0603R; Tolerance 0.1%; MPN RG1608P-101-B-T5
R10, R13, R16, R19: 3k3; 0603R; MPN RC0603FR-073K3L
R25: 11k5; 0603R; MPN RC0603FR-0711K5L
R26, R40: 6k65; 0603R; MPN RC0603FR-076K65L
R27, R28, R29, R30: 40k2; 0603R; Tolerance 0.1%; MPN RG1608P-4022-B-T5
R31, R32, R33, R34: 10k; 0603R; Tolerance 0.1%; MPN RG1608P-103-B-T5
R35, R36, R37, R38: 100k; 0603R; MPN RC0603FR-07100KL
R49: 93k1; 0603R; MPN RMCF0603FT93K1
R50: 10k; 0603R; MPN RC0603FR-0710KL
T2: TP_+24V_ADC; TestPad_Via
U9, U10, U11, U12: TPS26613DDFR; SOT-23-8; MPN TPS26613DDFR
U15: TPS7A4001DGN; HVSSOP-8-1EP; MPN TPS7A4001DGNR

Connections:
+12V_TPS: C43.1, C44.1, C45.1, C46.1, C50.1, R25.1, R49.1, U9.6 (+Vs), U10.6 (+Vs), U11.6 (+Vs), U12.6 (+Vs), U15.1 (OUT)
+24V_ADC: C4.1, C6.1, C56.1, F3.1, F4.1, F5.1, F6.1, R1.1, T2.1 (1_1), U15.5 (EN), U15.8 (IN); also elsewhere on the board
/1 Conectores/+24V_AIN1: D22.1 (K), D32.1 (K); also elsewhere on the board
/1 Conectores/+24V_AIN2: D19.1 (K), D33.1 (K); also elsewhere on the board
/1 Conectores/+24V_AIN3: D16.1 (K), D34.1 (K); also elsewhere on the board
/1 Conectores/+24V_AIN4: D13.1 (K), D35.1 (K); also elsewhere on the board
/1 Conectores/AIN1: D23.1 (K), U9.4 (IN); also elsewhere on the board
/1 Conectores/AIN2: D20.1 (K), U10.4 (IN); also elsewhere on the board
/1 Conectores/AIN3: D17.1 (K), U11.4 (IN); also elsewhere on the board
/1 Conectores/AIN4: D14.1 (K), U12.4 (IN); also elsewhere on the board
/5 ADC/AIN1_ADC: C41.2, D24.3 (COM), R19.1; also elsewhere on the board
/5 ADC/AIN2_ADC: C40.2, D21.3 (COM), R16.1; also elsewhere on the board
/5 ADC/AIN3_ADC: C39.2, D18.3 (COM), R13.1; also elsewhere on the board
/5 ADC/AIN4_ADC: C38.2, D15.3 (COM), R10.1; also elsewhere on the board
/6 Lacos 4-20mA/BRD_AIN1: D26.1 (K), Q1.3 (D), R18.2
/6 Lacos 4-20mA/BRD_AIN2: D27.1 (K), Q2.3 (D), R15.2
/6 Lacos 4-20mA/BRD_AIN3: D28.1 (K), Q3.3 (D), R12.2
/6 Lacos 4-20mA/BRD_AIN4: D29.1 (K), Q4.3 (D), R9.2
/6 Lacos 4-20mA/VSNS: C51.1, R25.2, R26.1, R40.1, U9.7 (VSNS), U10.7 (VSNS), U11.7 (VSNS), U12.7 (VSNS)
MODO_AIN1: Q1.1 (G), R35.1; also elsewhere on the board
MODO_AIN2: Q2.1 (G), R36.1; also elsewhere on the board
MODO_AIN3: Q3.1 (G), R37.1; also elsewhere on the board
MODO_AIN4: Q4.1 (G), R38.1; also elsewhere on the board
unnamed: D2.2 (A), R1.2
unnamed: D32.2 (A), F3.2
unnamed: D33.2 (A), F4.2
unnamed: D34.2 (A), F5.2
unnamed: D35.2 (A), F6.2
unnamed: FB3.1, R30.1, R34.1
unnamed: FB3.2, R10.2
unnamed: FB4.1, R29.1, R33.1
unnamed: FB4.2, R13.2
unnamed: FB5.1, R28.1, R32.1
unnamed: FB5.2, R16.2
unnamed: FB6.1, R27.1, R31.1
unnamed: FB6.2, R19.2
unnamed: R18.1, R27.2, U9.5 (OUT)
unnamed: R15.1, R28.2, U10.5 (OUT)
unnamed: R12.1, R29.2, U11.5 (OUT)
unnamed: R9.1, R30.2, U12.5 (OUT)
unnamed: R49.2, R50.1, U15.2 (FB)

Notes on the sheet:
CIN local do U15 > 1 uF efectivo (SBVS162B p.1 e p.13) desde 25-09;
p.110/107).
BRD_AINn; gate em MODO_AINn = P1-P4 do AD7124; 100k a GND).
9. +Vs dos protectores no +12V_TPS (era +5V_REG), NAO nos +24V_ADC:
18. Corridas 5/6 (I26): o rail +24V_ADC nao tem clamp proprio (o
(quebra-se em modo comum): e o I2t do fusivel - 0,2 mA2s contra
o corte de sobretensao de OUT fica a ~12,3 V: passa 10, corta 24.
55 us); burden 100R a GND; FB 470R; 3k3 + 100nF; BAT54S.
Tecto do rail: sem o D25, R49 ABERTA (nao a R50, que colapsa
~2,7 entregues: abre em ~3 us e o rail fica <= 9 V. Ver 16d/e. [Adenda 2026-09-15] D1 e D5 passam a onsemi MBR1H100SFT3G (100 V, SOD-123FL, mesmo land): o abs max do D1 deixa de depender do fusivel e da capacidade do rail (pior canto do B2-c8: 70,15 V < 100 V). F3-F6 ficam a 50 mA. D31 fica RB162MM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
17. Tanda 4c (ronda 7 I2-r7 e corrida 4 I17/I18): o requisito do
ponto = G = 1, S = 2 ao lado, D = 3 isolado; VGS(th) <= 1,45 V,
D200 fica antes do D1). O que protege o D1 (VR 60 V) nao e o RC
(E3/E4). C50 22uF/25V; C56 10uF/100V 1210 (25-09). 165 mW a 32V/8,2mA.
4-20 mA: Q fechado, tap = I x 100R x 0,199 = 0,40 V FE, ganho 4.
rev.F p.14 (10 mA em AINx) e CN-0384 Fig.5 (rede de entrada
15. kicad-happy 09-09: D15/18/21/24 BAT54S -> BAV199 (fuga 5 nA, nao
AIN2>AIN3_ADC, AIN3>AIN2_ADC, AIN4>AIN1_ADC. Preservado
dreno a GND (R18 limita a 0,33 A, ~27 uJ). Q1-Q4 = Q_NMOS 30 V
passa de 5,76 W continuos a 160 mW durante 100 ms (11% de
14. Decisoes 2026-09-04: Q1-Q4 = AO3400A (AOS rev.3.1 p.1, desenho:
DECISOES DESTA FOLHA (F2 2.2b)
7. D2 + R1 10k (2,1 mA): era 4k7 = 99 mW, 120% do 0603 a 85 C.
abaixo de 4,5 V (> 3,2 V a 32 mA). Rth 2k6: TI nao especifica a
4. CRUZAMENTO HERDADO da V2.2 (layout): campo AIN1>AIN4_ADC,
(corrida 8 B3). C56 = 10 uF 100 V 1210 (GRM32EC72A106ME05L):
protector a limitar a 32 mA o fusivel deixa de ter de proteger
burden a 0,1 %/25 ppm (Susumu RG1608P): 3 resistencias no ganho, a 1 %
antes vinha so do C4, a 7,1 mm (mesma correccao do C34 da legacy).
borne, antes do fusivel (netlist: +24V_AIN1 = D22.1+F3.2+P2.6).
(TPS2661x) e SLVAF40 (PTC vs protector, medidos); AD7124-8
R25 11k5 / R26 3k32, k = 4,46 (+Vs 12 V): sobe a 7,7 V; loop-pwr
OUT segue os 24 V > 12,3 V -> TPS corta, hiccup (1-5 us corte /
5. Cadeia por canal: TVS 824500301; TPS26613DDFR (limita a 32 mA em
generico (AO3400A) ate haver datasheet. Gama 0-10 V especificada
10. FONTES dos dimensionamentos desta folha: TI SLVSFE3C rev.C
servico) = 18 mW medios. Fica em 0603.
1. F3-F6 = 3413.0006.22 125 mA, 2,0 ohm, I2t 0,003 A2s (USFF p.3) -> D32-D35 MBR1H100SF serie -> D13/16/19/22 SMBJ51A junto a P2 (2026-09-25). Diodo bloqueia o retorno de surto do campo para o bus; SMBJ51A (VBR >= 56,7 V) nao conduz em surtos do bus (D1 grampeia <= 53,3 V): o clamp nunca passa no f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
LDO U15 TPS7A4001 na tanda 3 (nota 16): o R39 e o D25 NAO
0-10 V: Q aberto, 50k de entrada, tap 1,99 V FE, ganho 1. RON do
